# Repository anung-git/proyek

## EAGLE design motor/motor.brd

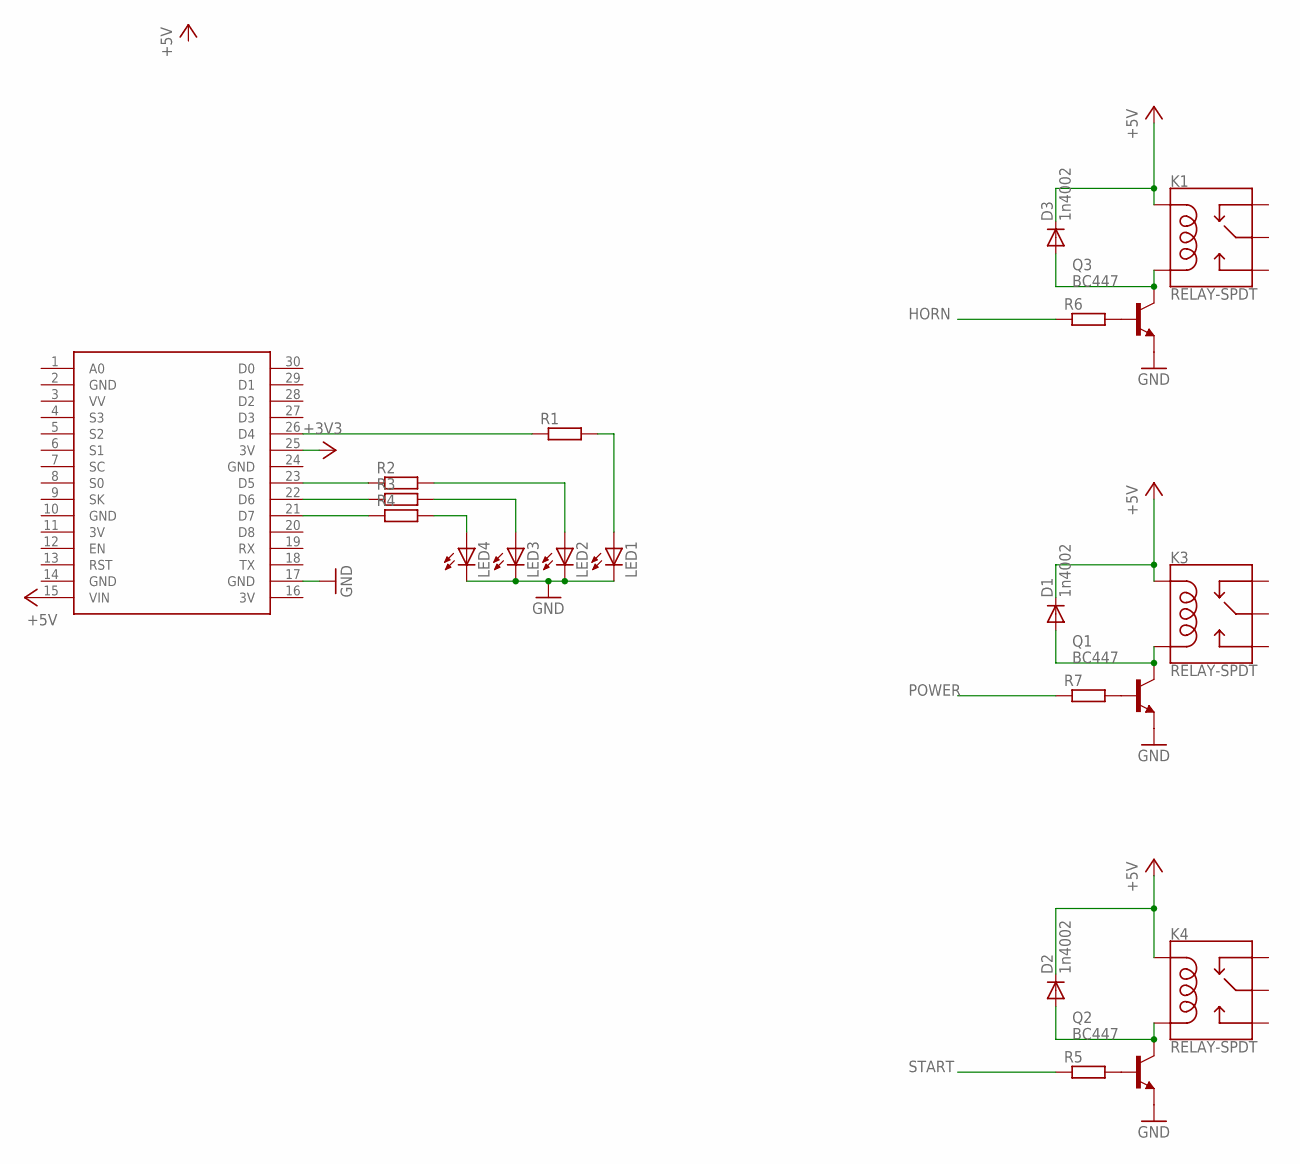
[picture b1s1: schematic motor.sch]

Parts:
D1, D2, D3: 1n4002; DO35-10
K1, K3, K4: RELAY-SPDT; RELAY_G5LE
LED1, LED2, LED3, LED4: LED5MM
Q1, Q2, Q3: BC447; TO92-EBC
R1, R2, R3, R4, R5, R6, R7: R-EU_0207/10; 0207/10
U$2: NODEMCU

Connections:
3V: U$2.11 (3V), U$2.16 (3V)
+3V3: U$2.25 (3V)
+5V: D1.C, D2.C, D3.C, K1.2 (COIL1), K3.2 (COIL1), K4.2 (COIL1), U$2.15 (VIN)
GND: LED1.K (C), LED2.K (C), LED3.K (C), LED4.K (C), Q1.E, Q2.E, Q3.E, U$2.2 (GND), U$2.10 (GND), U$2.14 (GND), U$2.17 (GND), U$2.24 (GND)
HORN: R6.1
unnamed: R1.1, U$2.26 (D4)
unnamed: D3.A, K1.5 (COIL2), Q3.C
unnamed: R3.1, U$2.22 (D6)
unnamed: R4.1, U$2.21 (D7)
unnamed: LED1.A, R1.2
unnamed: LED2.A, R2.2
unnamed: LED3.A, R3.2
unnamed: LED4.A, R4.2
unnamed: Q3.B, R6.2
unnamed: D2.A, K4.5 (COIL2), Q2.C
unnamed: Q2.B, R5.2
unnamed: R2.1, U$2.23 (D5)
unnamed: D1.A, K3.5 (COIL2), Q1.C
unnamed: Q1.B, R7.2
POWER: R7.1
START: R5.1

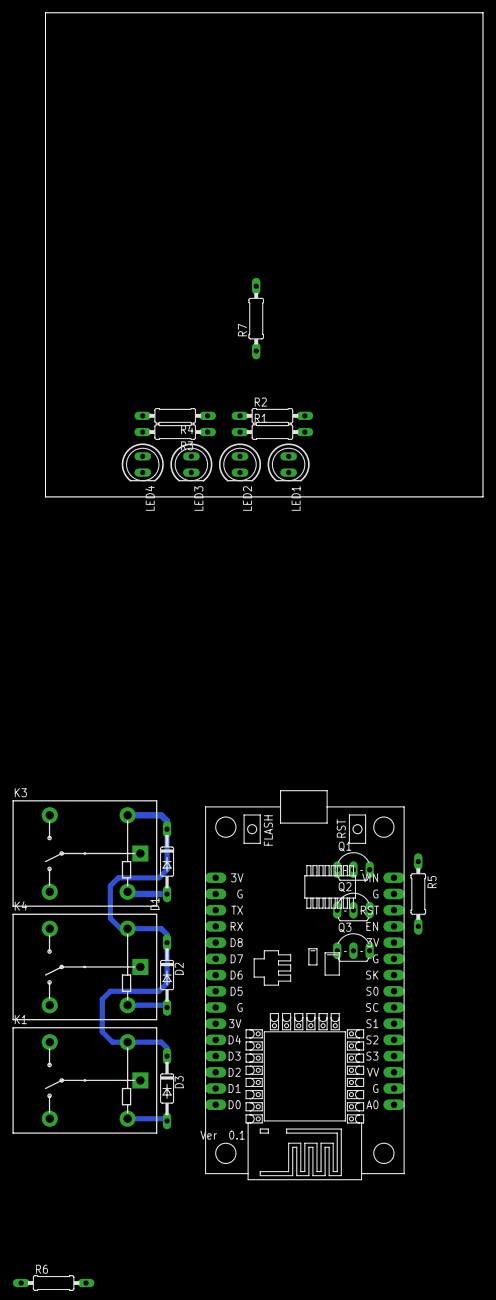
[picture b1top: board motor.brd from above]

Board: 2 copper layers, 68.6 x 75.9 mm, 21 parts (0 on the bottom side), 17 nets.

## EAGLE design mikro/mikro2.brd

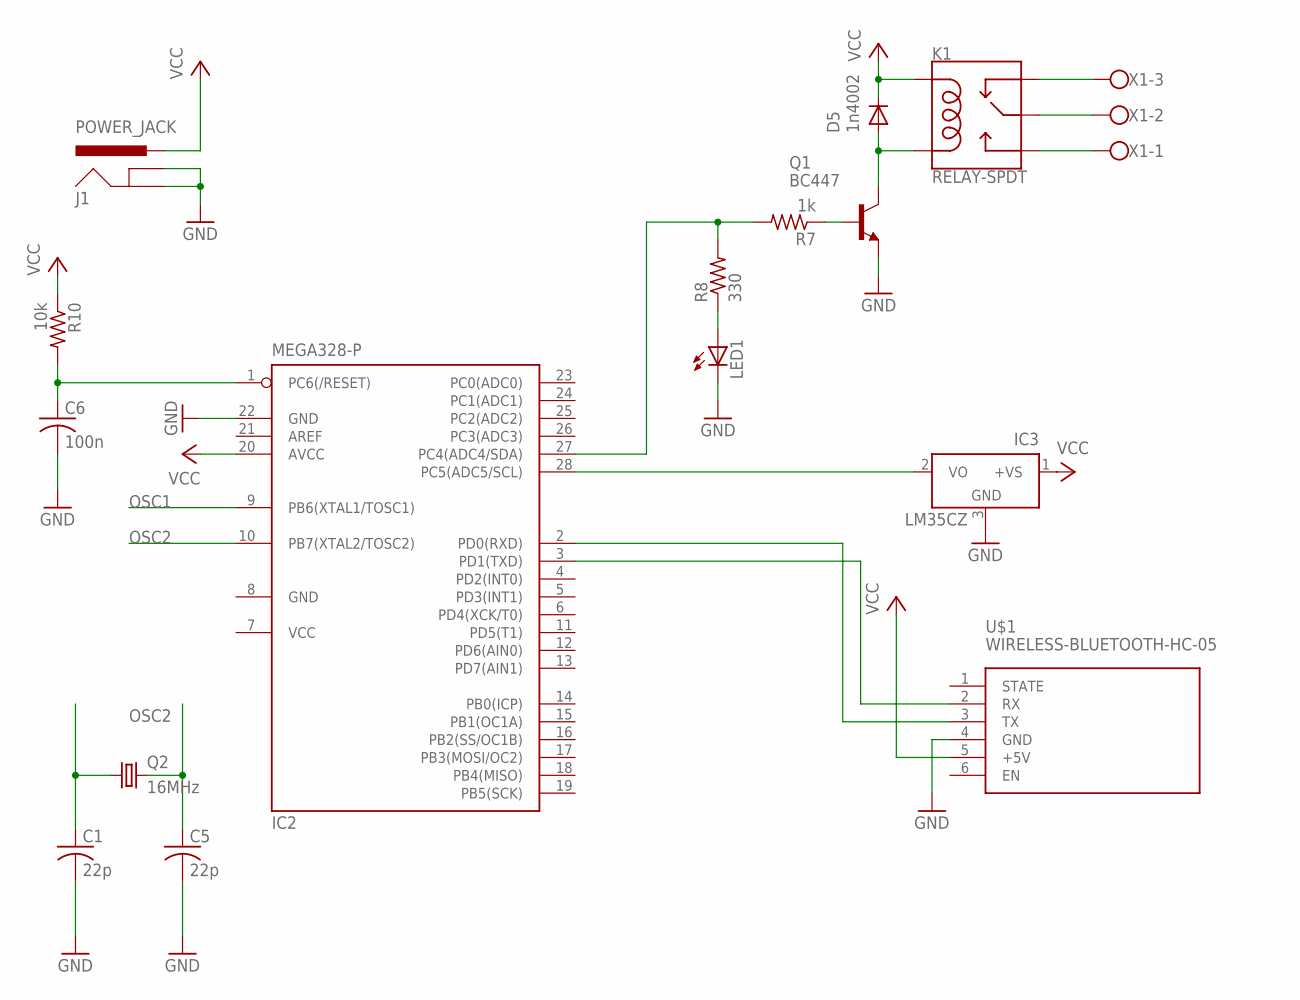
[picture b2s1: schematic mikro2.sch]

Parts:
C1, C5: 22p; C050-024X044
C6: 100n; C050-024X044
D5: 1n4002; DO35-10
IC2: MEGA328-P; DIL28-3
IC3: LM35CZ; TO92
J1: POWER_JACK; POWER_JACK_PTH
K1: RELAY-SPDT; RELAY_G5LE
LED1: LED5MM
Q1: BC447; TO92-EBC
Q2: 16MHz; HC49/S
R7: 1k; 0207/7
R8: 330; 0207/7
R10: 10k; 0207/7
U$1: WIRELESS-BLUETOOTH-HC-05
X1: W237-103

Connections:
GND: C1.2, C5.2, C6.2, IC2.8 (GND), IC2.22 (GND), IC3.3 (GND), J1.GND, J1.GNDBREAK, LED1.K (C), Q1.E, U$1.4 (GND)
unnamed: IC2.28 (PC5(ADC5/SCL)), IC3.2 (VO)
unnamed: K1.3 (NO), X1.1
unnamed: K1.1 (MAIN), X1.2
unnamed: K1.4 (NC), X1.3
unnamed: IC2.2 (PD0(RXD)), U$1.3 (TX)
unnamed: IC2.3 (PD1(TXD)), U$1.2 (RX)
unnamed: IC2.27 (PC4(ADC4/SDA)), R7.2, R8.2
unnamed: Q1.B, R7.1
unnamed: C6.1, IC2.1 (PC6(/RESET)), R10.2
unnamed: LED1.A, R8.1
unnamed: D5.A, K1.5 (COIL2), Q1.C
OSC1: C1.1, IC2.9 (PB6(XTAL1/TOSC1)), Q2.1
OSC2: C5.1, IC2.10 (PB7(XTAL2/TOSC2)), Q2.2
VCC: D5.C, IC2.7 (VCC), IC2.20 (AVCC), IC3.1 (+VS), J1.PWR, K1.2 (COIL1), R10.1, U$1.5 (+5V)

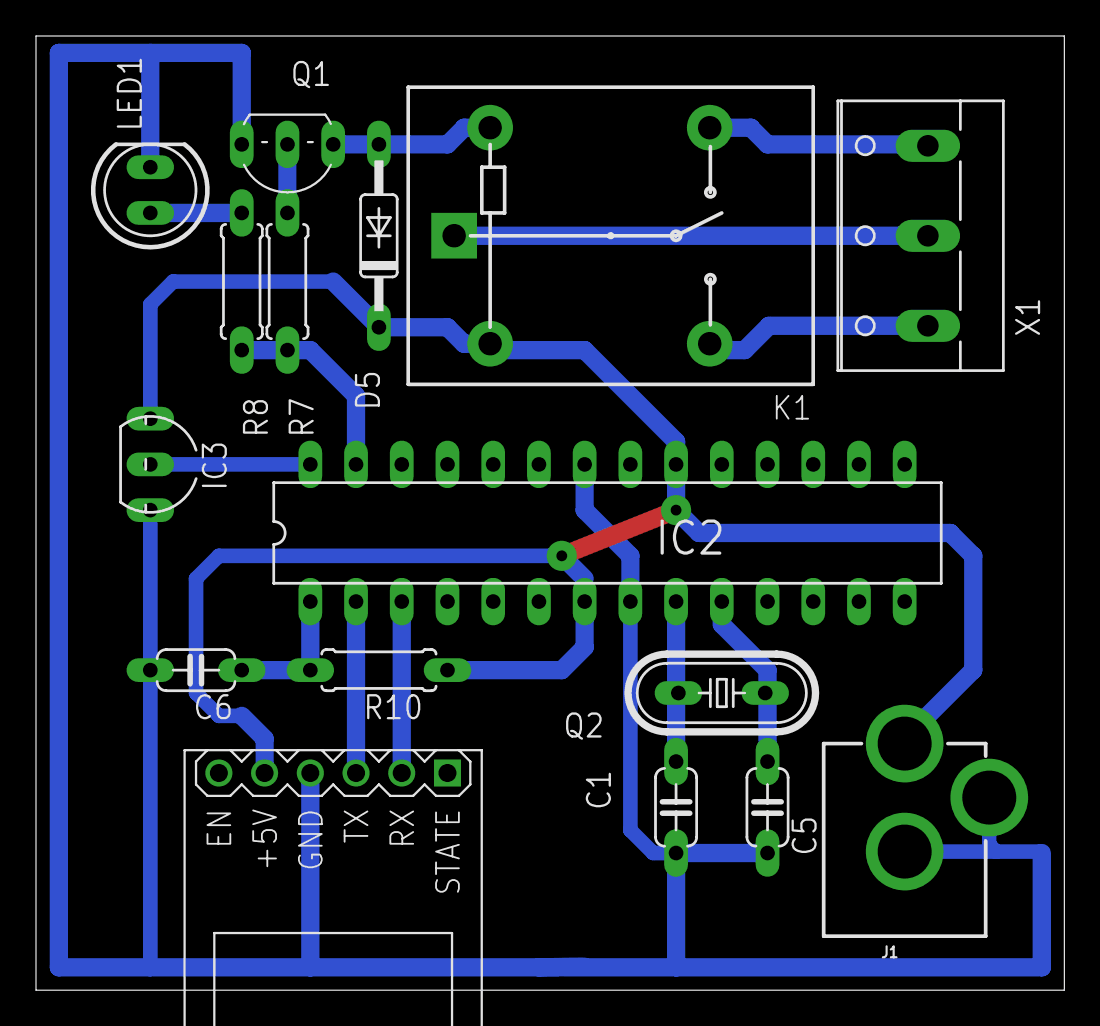
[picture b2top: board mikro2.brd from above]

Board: 2 copper layers, 57.1 x 53.0 mm, 16 parts (0 on the bottom side), 15 nets.

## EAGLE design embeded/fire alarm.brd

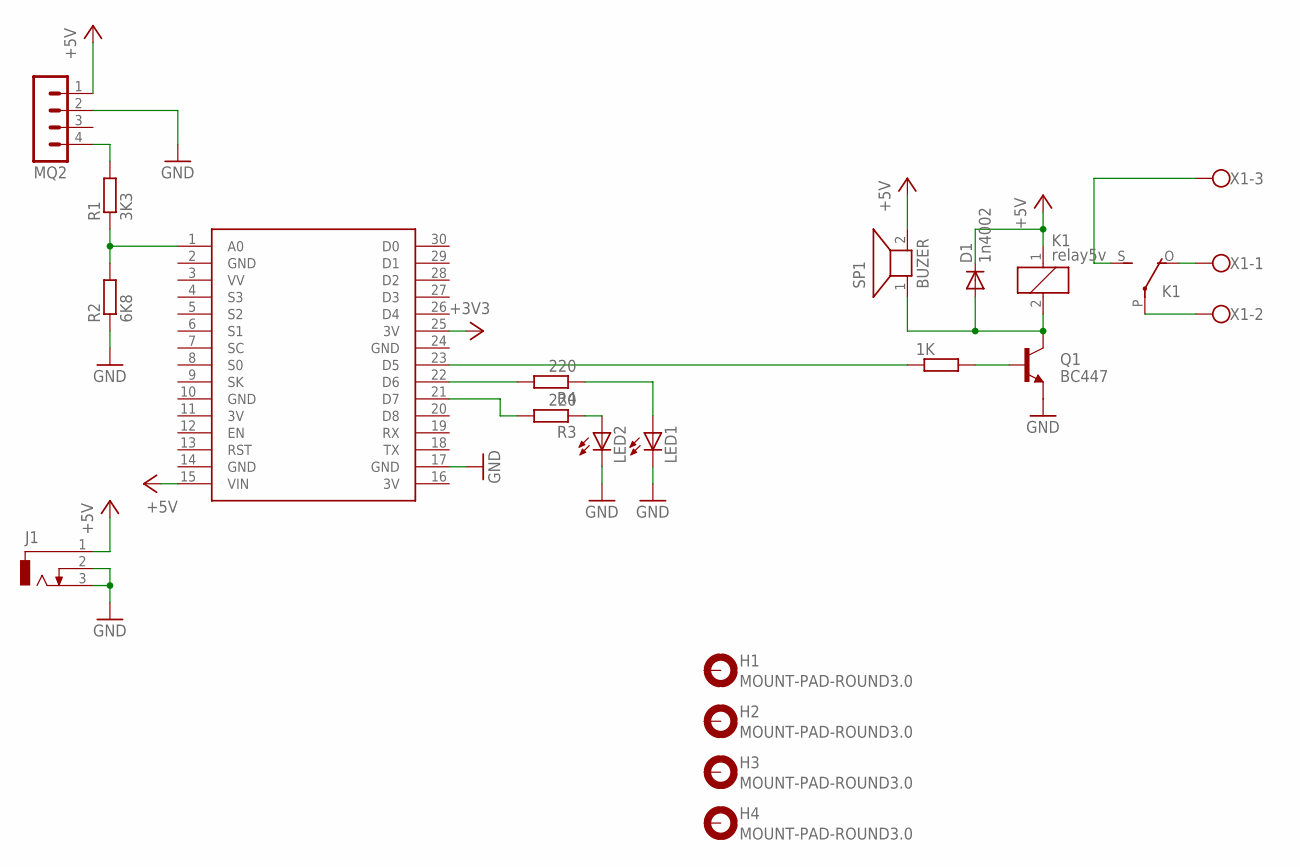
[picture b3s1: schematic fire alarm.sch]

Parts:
1K: R-EU_0207/10; 0207/10
D1: 1n4002; DO35-10
H1, H2, H3, H4: MOUNT-PAD-ROUND3.0; 3,0-PAD
J1: DCJ0303
K1: relay5v; ZF112
LED1, LED2: LED5MM
MQ2: MA04-1
Q1: BC447; TO92-EBC
R1: 3K3; 0207/10
R2: 6K8; 0207/10
R3, R4: 220; 0207/10
SP1: BUZER; AL60P
U$2: NODEMCU
X1: W237-103

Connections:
3V: U$2.11 (3V), U$2.16 (3V)
+3V3: U$2.25 (3V)
+5V: D1.C, J1.1, K1.1, MQ2.1, SP1.2, U$2.15 (VIN)
GND: J1.2, J1.3, LED1.K (C), LED2.K (C), MQ2.2, Q1.E, R2.1, U$2.2 (GND), U$2.10 (GND), U$2.14 (GND), U$2.17 (GND), U$2.24 (GND)
unnamed: 1K.1, U$2.23 (D5)
unnamed: R1.1, R2.2, U$2.1 (A0)
unnamed: MQ2.4, R1.2
unnamed: LED2.A, R3.1
unnamed: LED1.A, R4.1
unnamed: R4.2, U$2.22 (D6)
unnamed: R3.2, U$2.21 (D7)
unnamed: K1.S, X1.3
unnamed: D1.A, K1.2, Q1.C, SP1.1
unnamed: 1K.2, Q1.B
unnamed: K1.P, X1.2
unnamed: K1.O, X1.1

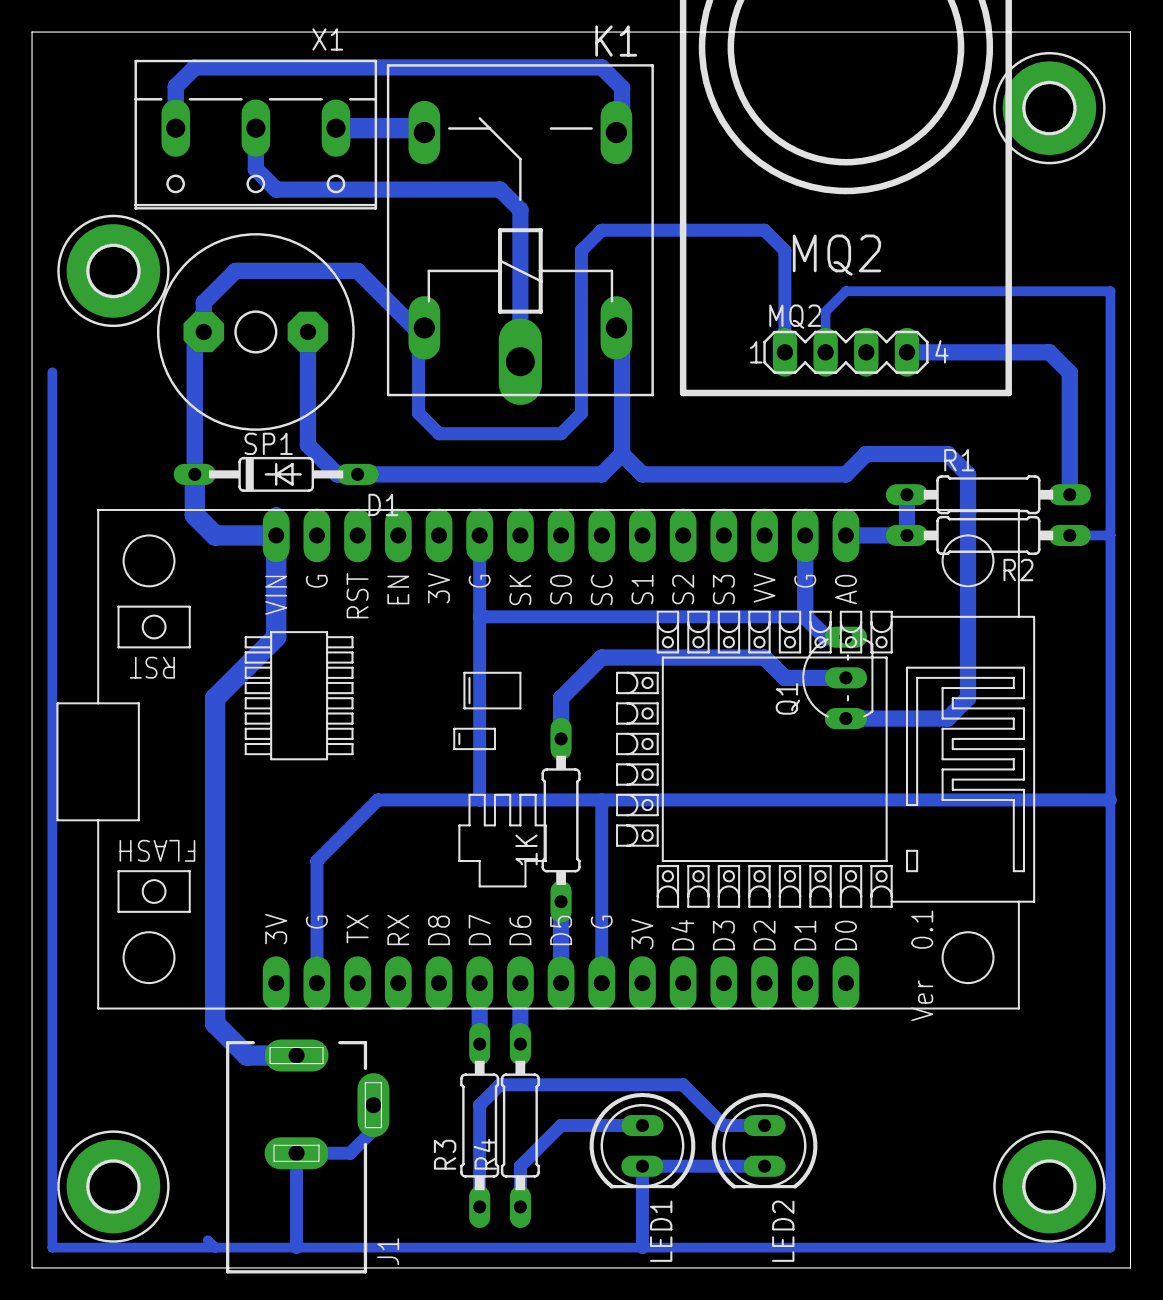
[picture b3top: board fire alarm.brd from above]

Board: 2 copper layers, 68.6 x 77.1 mm, 19 parts (0 on the bottom side), 15 nets.

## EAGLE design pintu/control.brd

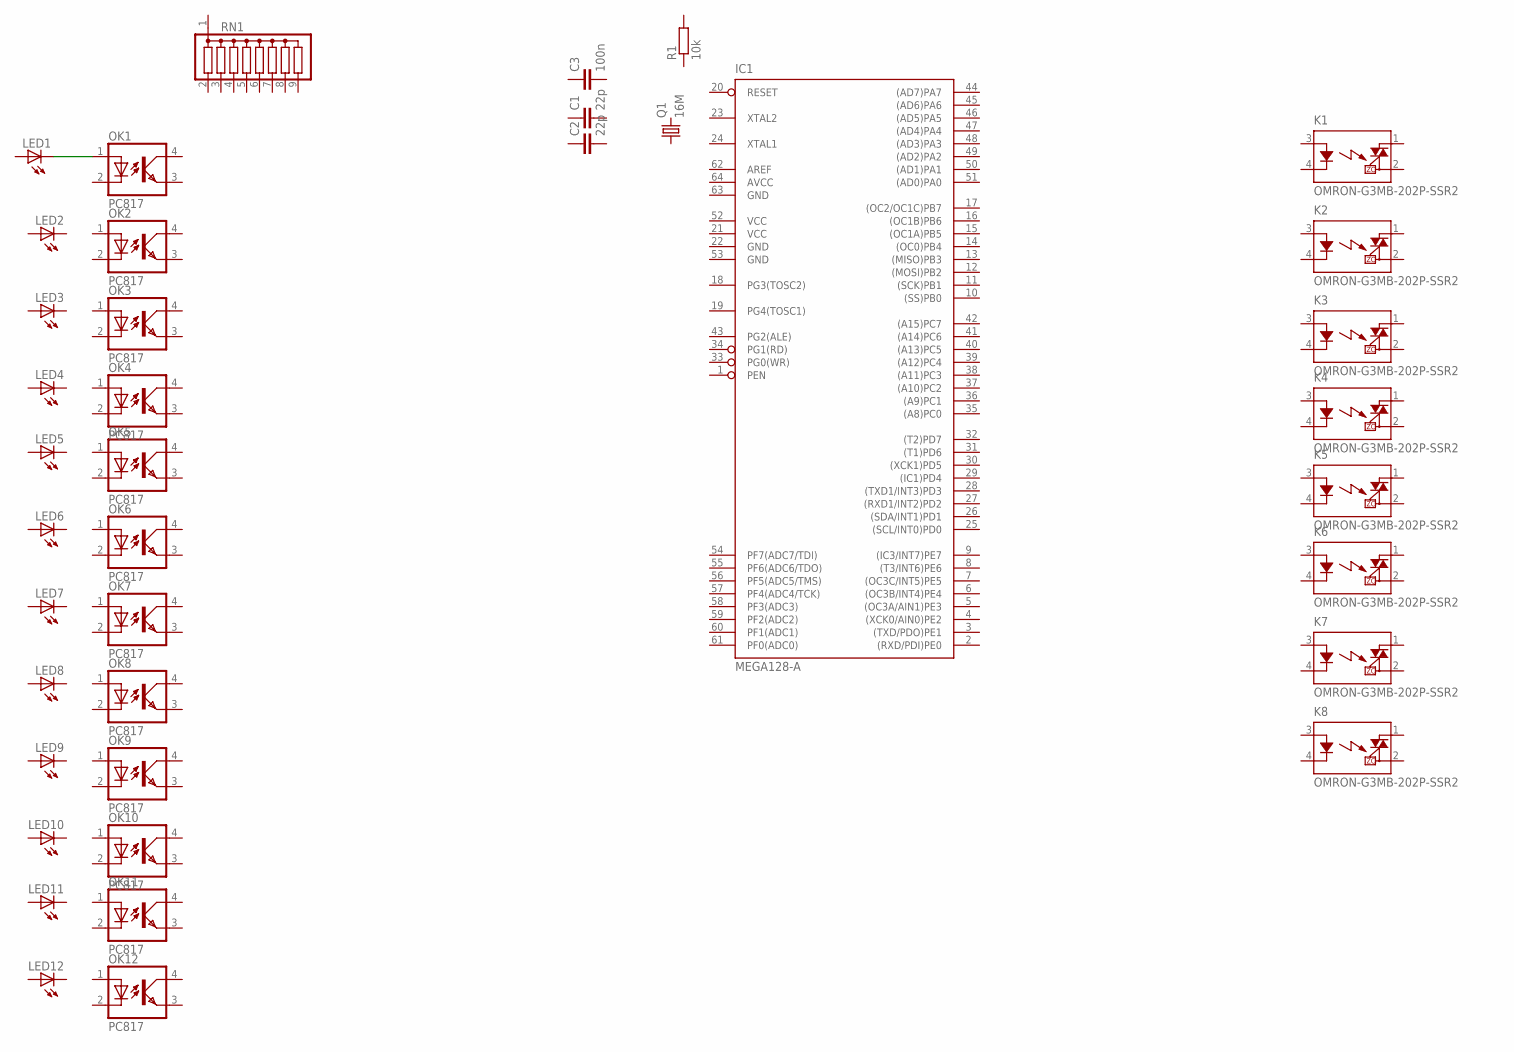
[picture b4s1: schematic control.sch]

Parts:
C1, C2: 22p; C025-025X050
C3: 100n; C025-025X050
IC1: MEGA128-A; TQFP64
K1, K2, K3, K4, K5, K6, K7, K8: OMRON-G3MB-202P-SSR2; OMRON-G3MB-202P-SSR
LED1, LED2, LED3, LED4, LED5, LED6, LED7, LED8, LED9, LED10, LED11, LED12: LED3MM
OK1, OK2, OK3, OK4, OK5, OK6, OK7, OK8, OK9, OK10, OK11, OK12: PC817; DIL04
Q1: 16M; HC49U-V
R1: 10k; 0207/10
RN1: G08R; SIL9

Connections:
AVCC: IC1.64 (AVCC)
GND: IC1.22 (GND), IC1.53 (GND), IC1.63 (GND)
unnamed: LED1.K (C), OK1.1 (A)
VCC: IC1.21 (VCC), IC1.52 (VCC)

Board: 2 copper layers, 39 parts (0 on the bottom side), 3 nets, no tracks yet.

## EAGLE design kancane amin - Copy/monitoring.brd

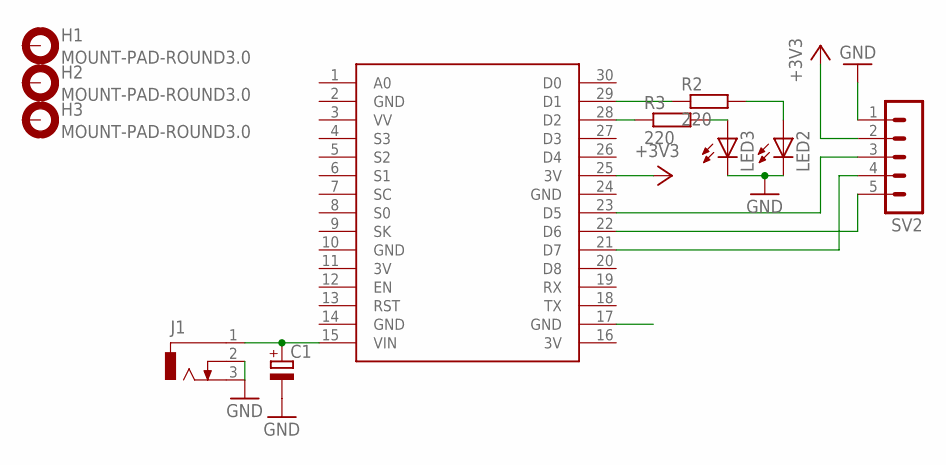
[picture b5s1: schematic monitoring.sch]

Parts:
C1: CPOL-EUE3.5-8; E3,5-8
H1, H2, H3: MOUNT-PAD-ROUND3.0; 3,0-PAD
J1: DCJ0303
LED2, LED3: LED5MM
R2, R3: 220; 0207/10
SV2: MA05-1
U$2: NODEMCU

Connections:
3V: U$2.11 (3V), U$2.16 (3V)
+3V3: SV2.2, U$2.25 (3V)
GND: C1.-, J1.2, J1.3, LED2.K (C), LED3.K (C), SV2.1, U$2.2 (GND), U$2.10 (GND), U$2.14 (GND), U$2.24 (GND)
unnamed: SV2.5, U$2.22 (D6)
unnamed: R2.1, U$2.29 (D1)
unnamed: SV2.4, U$2.21 (D7)
unnamed: SV2.3, U$2.23 (D5)
unnamed: R3.1, U$2.28 (D2)
unnamed: LED2.A, R2.2
unnamed: LED3.A, R3.2
unnamed: C1.+, J1.1, U$2.15 (VIN)

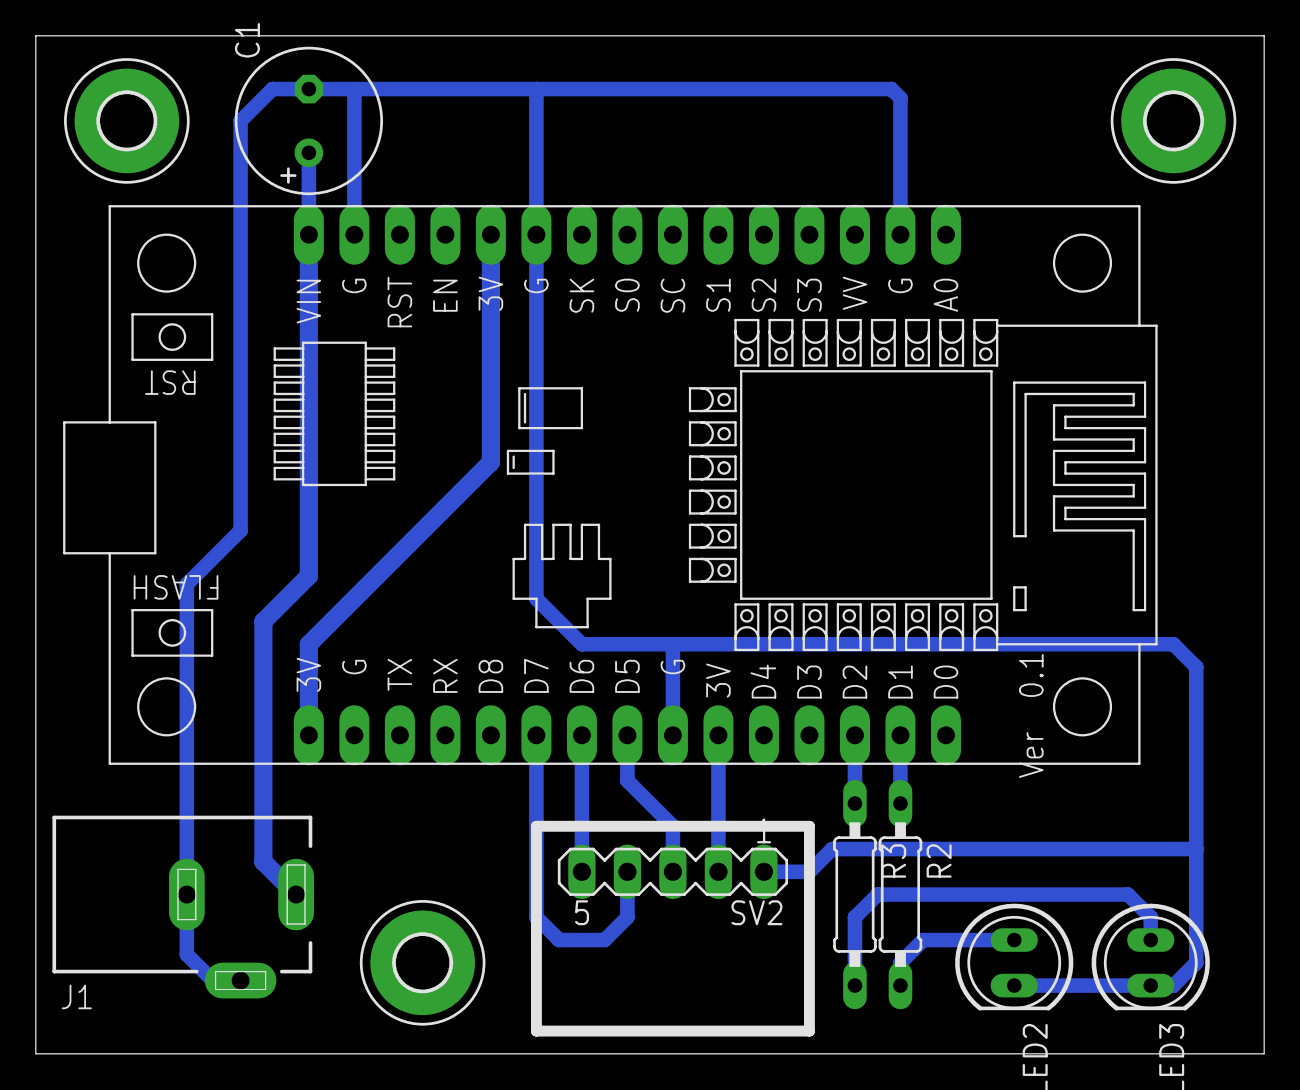
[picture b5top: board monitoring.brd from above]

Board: 2 copper layers, 68.6 x 56.8 mm, 11 parts (0 on the bottom side), 11 nets.

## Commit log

2019-12-10 upload
2019-12-10 delete
2019-12-11 mikro2
2019-12-15 harga
2019-12-15 motor
2019-12-19 program mikro
2020-02-02 edit lib

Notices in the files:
parts and their libraries:
SparkFun-Connectors: Licensing: Creative Commons ShareAlike 4.0 International - https://creativecommons.org/licenses/by-sa/4.0
diy-modules: Released under the Creative Commons Attribution 4.0 International License: http://creativecommons.org/licenses/by/4.0
